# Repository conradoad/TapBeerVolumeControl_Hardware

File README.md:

# Tap Beer Flow Control - Hardware

Hardware developed to control the volume dispensed from a tap beer (or any other liquid, such as water).

View the testing firmware in this repository: [TapBeerVolumeControl_Firmware](https://github.com/conradoad/TapBeerVolumeControl_Firmware)

## Hardware Components

- ESP32 DevKitC

- Flow Sensor

- Solenoid Valve

## Mounted PCB

- Schematic (KiCAD)

- PCB Layout (KiCAD)

- Prototype (using a router CNC)

## Demo Video

TODO: upload video

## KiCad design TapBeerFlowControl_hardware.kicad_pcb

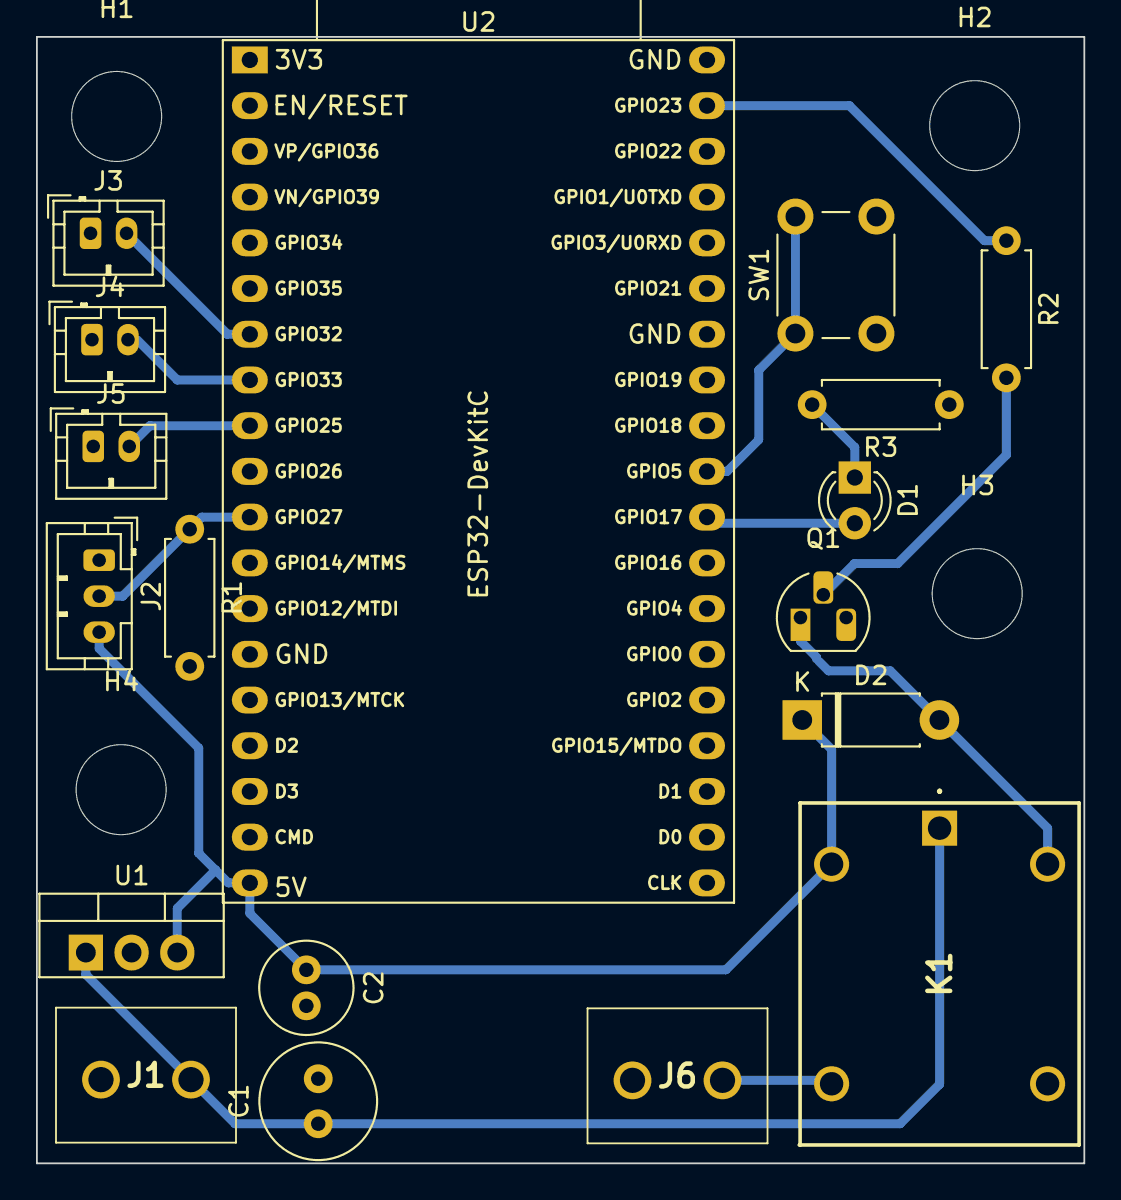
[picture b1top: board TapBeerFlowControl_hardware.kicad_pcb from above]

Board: 2 copper layers, 58.2 x 62.6 mm, 22 parts (0 on the bottom side), 14 nets.

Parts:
C1: 10u; C_Radial_D6.3mm_H11.0mm_P2.50mm
C2: 1u; C_Radial_D5.0mm_H11.0mm_P2.00mm
D1: LED; LED_D3.0mm
D2: 1N4001; D_DO-41_SOD81_P7.62mm_Horizontal
H1, H2, H3, H4: MountingHole; MountingHole_5mm
J1: 12_VIN; KF3012P
J2: SENSOR; JST_PH_B3B-PH-K_1x03_P2.00mm_Vertical
J3: SEL1; JST_PH_B2B-PH-K_1x02_P2.00mm_Vertical
J4: SEL2; JST_PH_B2B-PH-K_1x02_P2.00mm_Vertical
J5: SEL3; JST_PH_B2B-PH-K_1x02_P2.00mm_Vertical
J6: VALVE_OUT; KF3012P
K1: JQC-3FC_T73_DC05V; JQC3FCT73DC05V
Q1: BC547; TO-92_HandSolder
R1, R3: 18k; R_Axial_DIN0207_L6.3mm_D2.5mm_P7.62mm_Horizontal
R2: 1K; R_Axial_DIN0207_L6.3mm_D2.5mm_P7.62mm_Horizontal
SW1: SW_DIP_x01; SW_PUSH_6mm_H8mm
U1: LM7805_TO220; TO-220-3_Vertical
U2: ESP32-DevKitC

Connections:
+5V: C2.1, D2.1 (K), J2.3, K1.2 (COIL_1), U1.3 (VO), U2.19 (5V)
+12V: C1.1, J1.2, K1.1 (COM), U1.1 (VI)
/SEL1: J3.2, U2.7 (32K_XP/GPIO32/ADC1_CH4)
/SEL2: J4.2, U2.8 (32K_XN/GPIO33/ADC1_CH5)
/SEL3: J5.2, U2.9 (DAC_1/ADC2_CH8/GPIO25)
GND: C1.2, C2.2, J1.1, J2.1, J3.1, J4.1, J5.1, J6.1, Q1.3 (E), R1.2, R3.1, SW1.2, U1.2 (GND), U2.14 (GND), U2.32 (GND), U2.38 (GND)
unnamed: D1.2 (A), U2.28 (GPIO17)
unnamed: D1.1 (K), R3.2
unnamed: D2.2 (A), K1.5 (COIL_2), Q1.1 (C)
unnamed: J2.2, R1.1, U2.11 (ADC2_CH7/GPIO27)
unnamed: J6.2, K1.3 (N/O)
unnamed: Q1.2 (B), R2.2
unnamed: SW1.1, U2.29 (GPIO5)
unnamed: R2.1, U2.37 (GPIO23)

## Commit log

2023-12-05 adjust pending tasks in TODO file
2024-12-16 commit before system update
